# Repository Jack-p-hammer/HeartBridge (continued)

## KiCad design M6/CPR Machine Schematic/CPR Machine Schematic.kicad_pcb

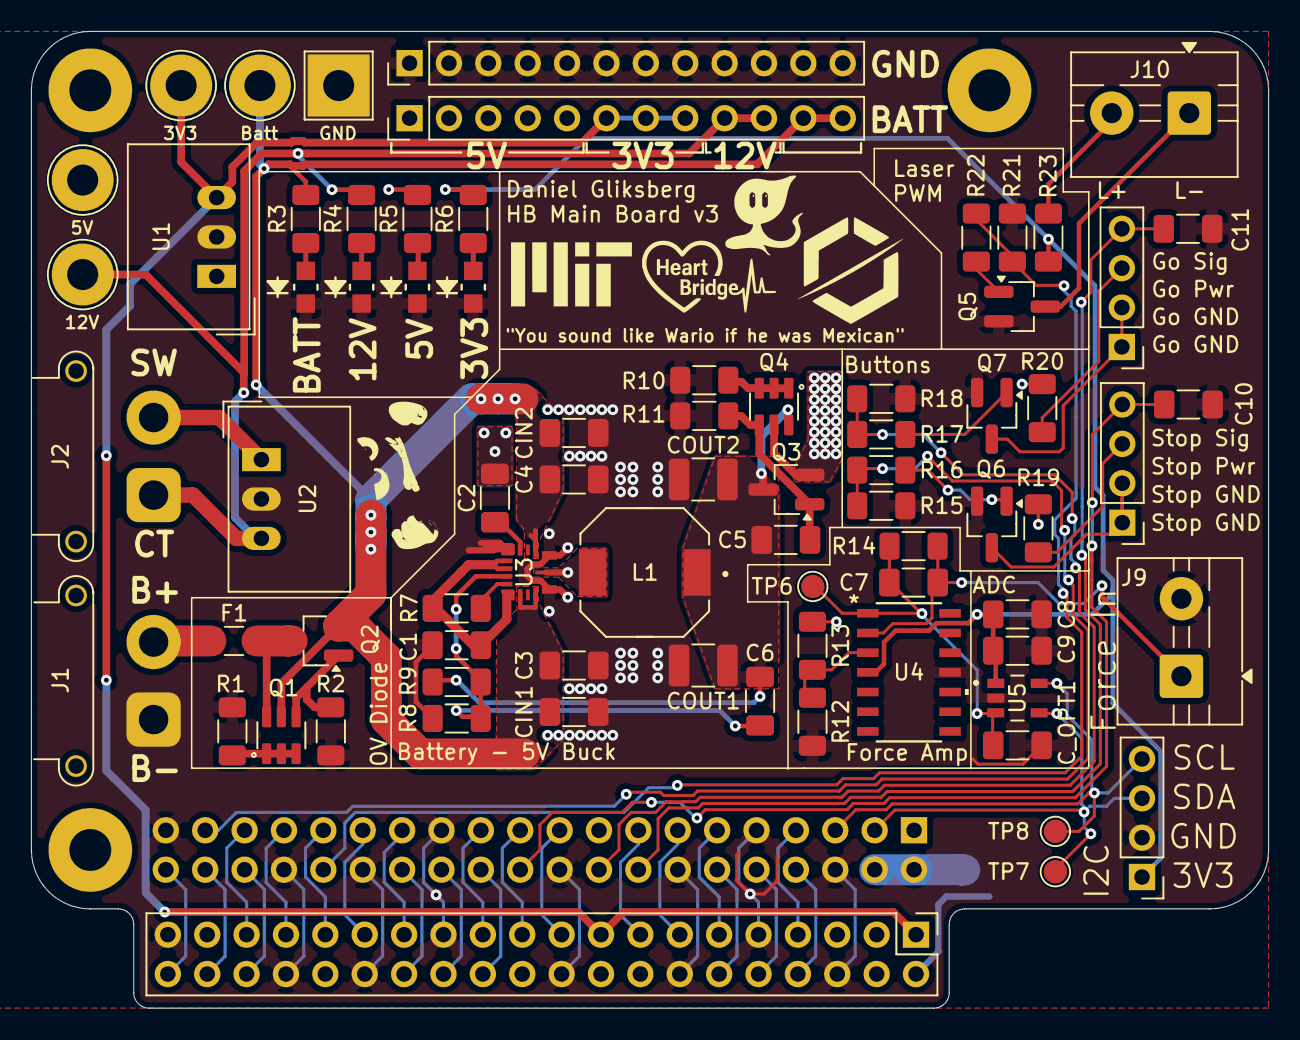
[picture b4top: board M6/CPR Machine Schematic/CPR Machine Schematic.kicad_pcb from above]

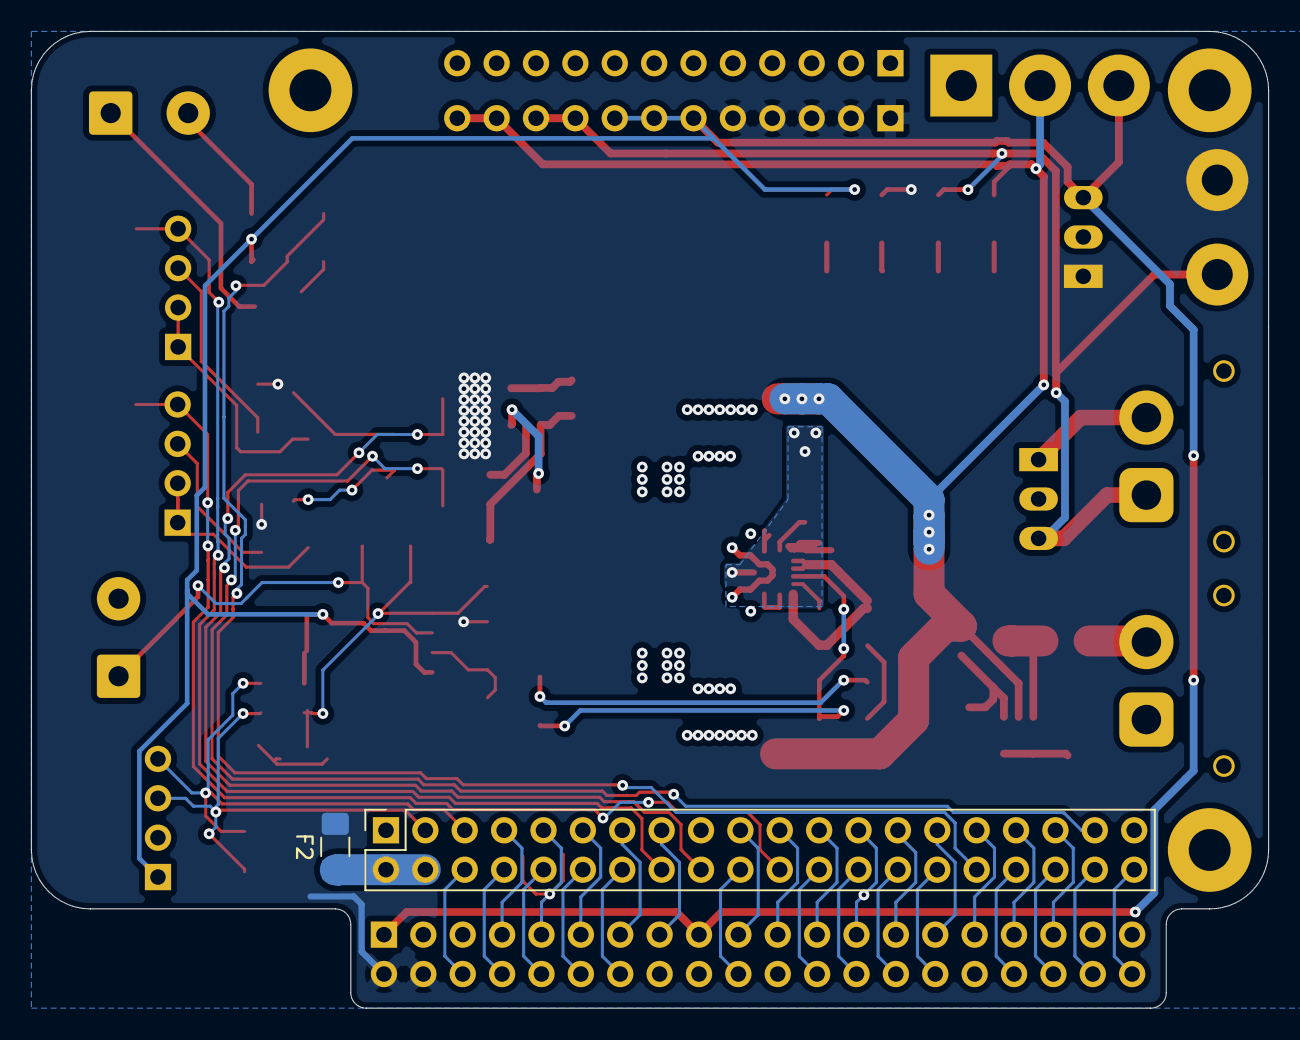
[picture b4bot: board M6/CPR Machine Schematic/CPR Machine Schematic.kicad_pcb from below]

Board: 2 copper layers, 79.8 x 63.0 mm, 80 parts (2 on the bottom side), 63 nets.

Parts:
C1: 2.2 uF; C_1206_3216Metric_Pad1.33x1.80mm_HandSolder
C2, C3, C4, C9: 0.1 uF; C_1206_3216Metric_Pad1.33x1.80mm_HandSolder
C5: 10 nF; C_1206_3216Metric_Pad1.33x1.80mm_HandSolder
C6, C7: 47 pF; C_1206_3216Metric_Pad1.33x1.80mm_HandSolder
C8: 10 uF; C_1206_3216Metric_Pad1.33x1.80mm_HandSolder
C10, C11: 100 nF; C_1206_3216Metric_Pad1.33x1.80mm_HandSolder
CIN1, CIN2: 2.2 uF; C_1206_3216Metric_Pad1.33x1.80mm_HandSolder
COUT1, COUT2: 23.7 uF; C_1210_3225Metric_Pad1.33x2.70mm_HandSolder
C_OPT1: 47 pF; C_1206_3216Metric_Pad1.33x1.80mm_HandSolder
F1: 4A; Fuse_1206_3216Metric_Pad1.42x1.75mm_HandSolder
F2: 3A; Fuse_1206_3216Metric_Pad1.42x1.75mm_HandSolder
H1, H2, H3: MountingHole; MountingHole_2.7mm_M2.5_Pad
J1: Battery 22.2V IN; AMASS_XT30PW-F_1x02_P2.50mm_Horizontal
J2: Power Switch; AMASS_XT30PW-F_1x02_P2.50mm_Horizontal
J3: GND Spare Headers; PinHeader_1x12_P2.54mm_Vertical
J4: +V Spare Headers; PinHeader_1x12_P2.54mm_Vertical
J5: Conn_02x20_Odd_Even; PinHeader_2x20_P2.54mm_Vertical
J6: I2C Port; PinHeader_1x04_P2.54mm_Vertical
J7: Stop Button Port; PinHeader_1x04_P2.54mm_Vertical
J8: Go Button Port; PinHeader_1x04_P2.54mm_Vertical
J9: Force Sensor; TerminalBlock_MaiXu_MX126-5.0-02P_1x02_P5.00mm
J10: Laser Port; TerminalBlock_MaiXu_MX126-5.0-02P_1x02_P5.00mm
J11: Raspberry_Pi_2_3; PinSocket_2x20_P2.54mm_Vertical
L1: 2.2 uH; IND_1217AS-H-2R2N=P3
LED1, LED2, LED3, LED4: Green; LED_LTST-C170GKT_LTO
Q1, Q4: DMMT5401 PNP; SOT95P285X140-6N
Q2: SSM3J332R; SOT-23_Handsoldering
Q3: DMG2305UX-EV; SOT-23_Handsoldering
Q5, Q6, Q7: T2N7002BK,LM; SOT-23_Handsoldering
R1, R10, R12, R15, R18, R21: 10 kOhm; R_1206_3216Metric_Pad1.30x1.75mm_HandSolder
R2, R11: 47 kOhm; R_1206_3216Metric_Pad1.30x1.75mm_HandSolder
R3: 1.5 kOhm; R_1206_3216Metric_Pad1.30x1.75mm_HandSolder
R4: 665 Ohm; R_1206_3216Metric_Pad1.30x1.75mm_HandSolder
R5: 220 Ohm; R_1206_3216Metric_Pad1.30x1.75mm_HandSolder
R6, R16, R17, R22: 100 Ohm; R_1206_3216Metric_Pad1.30x1.75mm_HandSolder
R7: 20 kOhm; R_1206_3216Metric_Pad1.30x1.75mm_HandSolder
R8: 9.5 kOhm; R_1206_3216Metric_Pad1.30x1.75mm_HandSolder
R9: 49.9 kOhm; R_1206_3216Metric_Pad1.30x1.75mm_HandSolder
R13: 90 kOhm; R_1206_3216Metric_Pad1.30x1.75mm_HandSolder
R14: 80.6 kOhm; R_1206_3216Metric_Pad1.30x1.75mm_HandSolder
R19, R20: 49.9 Ohm; R_1206_3216Metric_Pad1.30x1.75mm_HandSolder
R23: 0 Ohm; R_1206_3216Metric_Pad1.30x1.75mm_HandSolder
TP1: 12 V; TestPoint_THTPad_D4.0mm_Drill2.0mm
TP2: 5 V; TestPoint_THTPad_D4.0mm_Drill2.0mm
TP3: 3V3; TestPoint_THTPad_D4.0mm_Drill2.0mm
TP4: Battery; TestPoint_THTPad_D4.0mm_Drill2.0mm
TP5: GND; TestPoint_THTPad_4.0x4.0mm_Drill2.0mm
TP6: Amp Out; TestPoint_Pad_D1.5mm
TP7: SDA; TestPoint_Pad_D1.5mm
TP8: SCL; TestPoint_Pad_D1.5mm
U1: 3.3V Buck; Converter_DCDC_TRACO_TSR-1_THT
U2: 12V Buck; Converter_DCDC_TRACO_TSR-1_THT
U3: MAX42403AFLB+; 21-100701_90-100241_ADI
U4: MCP6004; SOIC14_SL_MCH
U5: MCP3021A5T-E_OT; IC_MCP3021A0T-E_OT

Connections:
+3.3V: C8.2, C9.2, J4.6, J4.7, J4.8, J5.1, J5.17, J6.1, R6.2, R23.1, TP3.1, U1.3 (Vout), U4.4 (V+), U5.1 (VDD)
+5V: F2.1, J4.1, J4.2, J4.3, J4.4, J4.5, J5.2, J5.4, Q3.2, Q4.5, R5.2, R13.1, R19.2, R20.2, TP2.1, U1.1 (Vin)
+12V: J2.1, J4.9, J4.10, R4.2, TP1.1, U2.3 (Vout)
+22.2V: C3.2, C4.2, CIN1.2, CIN2.2, J4.11, J4.12, Q1.5, Q2.2, R3.2, TP4.1, U3.1 (EN), U3.3 (SUP), U3.7 (SUP)
/HMI_Raspi/Go Button: C11.2, J8.4, J11.16 (GPIO23)
/HMI_Raspi/Go Button Ground: J8.1, J8.2, Q7.3 (D)
/HMI_Raspi/Go LED Power: J8.3, R20.1
/HMI_Raspi/Go_Enable: J11.18 (GPIO24), R17.1, R18.1
/HMI_Raspi/Laser_PWM: J11.32 (PWM0/GPIO12), R21.1, R22.1
/HMI_Raspi/Stop Button: C10.2, J7.4, J11.22 (GPIO25)
/HMI_Raspi/Stop Button Ground: J7.1, J7.2, Q6.3 (D)
/HMI_Raspi/Stop LED Power: J7.3, R19.1
/HMI_Raspi/Stop_Enable: J11.37 (GPIO26), R15.1, R16.1
/Power/BST: C2.2, U3.9 (BST)
/Power/Battery +: F1.1, J1.2
/Power/From Switch: J2.2, U2.1 (Vin)
/Power/LX: C2.1, L1.2, U3.5 (LX)
/Power/Reg OUT: C5.2, C6.2, COUT1.1, COUT2.1, L1.1, Q3.3, Q4.6, R9.1
/Raspi/GPIO0: J5.27, J11.27 (ID_SD/GPIO0)
/Raspi/GPIO1: J5.28, J11.28 (ID_SC/GPIO1)
/Raspi/GPIO4: J5.7, J11.7 (GCLK0/GPIO4)
/Raspi/GPIO5: J5.29, J11.29 (GCLK1/GPIO5)
/Raspi/GPIO6: J5.31, J11.31 (GCLK2/GPIO6)
/Raspi/GPIO7: J5.26, J11.26 (~CE1/GPIO7)
/Raspi/GPIO8: J5.24, J11.24 (~CE0/GPIO8)
/Raspi/GPIO9: J5.21, J11.21 (MISO0/GPIO9)
/Raspi/GPIO10: J5.19, J11.19 (MOSI0/GPIO10)
/Raspi/GPIO11: J5.23, J11.23 (SCLK0/GPIO11)
/Raspi/GPIO13: J5.33, J11.33 (PWM1/GPIO13)
/Raspi/GPIO14: J5.8, J11.8 (GPIO14/TXD)
/Raspi/GPIO15: J5.10, J11.10 (GPIO15/RXD)
/Raspi/GPIO16: J5.36, J11.36 (GPIO16)
/Raspi/GPIO17: J5.11, J11.11 (GPIO17)
/Raspi/GPIO18: J5.12, J11.12 (GPIO18/PWM0)
/Raspi/GPIO19: J5.35, J11.35 (GPIO19/MISO1)
/Raspi/GPIO20: J5.38, J11.38 (GPIO20/MOSI1)
/Raspi/GPIO21: J5.40, J11.40 (GPIO21/SCLK1)
/Raspi/GPIO22: J5.15, J11.15 (GPIO22)
/Raspi/GPIO27: J5.13, J11.13 (GPIO27)
/Raspi/I2C_SCL: J6.4, J11.5 (SCL/GPIO3), TP8.1, U5.5 (SCL)
/Raspi/I2C_SDA: J6.3, J11.3 (SDA/GPIO2), TP7.1, U5.4 (SDA)
/Sensing/Vref: R12.1, R13.2, U4.3 (+)
GND: C1.1, C3.1, C4.1, C8.1, C9.1, C10.1, C11.1, CIN1.1, CIN2.1, COUT1.2, COUT2.2, C_OPT1.1, J1.1, J3.1, J3.2, J3.3, J3.4, J3.5, J3.6, J3.7, J3.8, J3.9, J3.10, J3.11, J3.12, J5.6, J5.9, J5.14, J5.20, J5.25, J5.30, J5.34, J5.39, J6.2, J9.2, J11.6 (GND), J11.9 (GND), J11.14 (GND), J11.20 (GND), J11.25 (GND), J11.30 (GND), J11.34 (GND), J11.39 (GND), LED1.1, LED2.1, LED3.1, LED4.1, Q5.2 (S), Q6.2 (S), Q7.2 (S), R1.2, R2.2, R8.2, R10.2, R11.2, R12.2, R15.2, R18.2, R21.2, TP5.1, U1.2 (GND), U2.2 (GND), U3.4 (PGND), U3.6 (PGND), U3.10 (GND), U4.11 (V-), U5.2 (VSS)
unnamed: C5.1, Q3.1, Q4.4, R11.1
unnamed: F1.2, Q1.6, Q2.3
unnamed: F2.2, J11.2 (5V), J11.4 (5V)
unnamed: C7.1, J9.1, R14.2, U4.2 (-)
unnamed: J10.1, Q5.3 (D)
unnamed: J10.2, R23.2
unnamed: LED1.2, R4.1
unnamed: LED2.2, R3.1
unnamed: LED3.2, R5.1
unnamed: LED4.2, R6.1
unnamed: Q1.1, Q1.2, Q1.3, R1.1
unnamed: Q1.4, Q2.1, R2.1
unnamed: Q4.1, Q4.2, Q4.3, R10.1
unnamed: Q5.1 (G), R22.2
unnamed: Q6.1 (G), R16.2
unnamed: Q7.1 (G), R17.2
unnamed: C1.2, R7.2, U3.11 (BIAS), U3.12 (SPS), U3.15 (SYNC)
unnamed: C6.1, R8.1, R9.2, U3.13 (FB)
unnamed: R7.1, U3.14 (PGOOD)
unnamed: C7.2, C_OPT1.2, R14.1, TP6.1, U4.1, U5.3 (AIN)

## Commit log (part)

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2026-03-29 Battery Tracking
2026-03-29 Audio buzzing fixed
2026-04-28 Final PCB
2026-05-07 PCB V1 Final
2026-05-10 Code V3 Start
2026-05-11 Barebones state machine
2026-05-19 test for pulling on pi
2026-05-19 Uploaded images and audio files
2026-05-19 Set up package management
2026-05-19 Package Management part 2
2026-05-19 attempting to sensor
2026-05-19 AV Initialization
2026-05-19 Image Display maybe?
2026-05-19 Some file structure refactoring
2026-06-02 Start of Board V2
2026-06-02 Fixed edge cuts
2026-06-07 Board V2
2026-06-12 Board V2 Final
2026-06-18 Printing Files
2026-06-18 middle printing file
2026-06-22 more printing files
2026-06-26 Final PCB V2
2026-06-28 Python code started
    run:
    pip install -r requirements.txt
    in the project directory on your device to download required packages
2026-06-28 File structure, claude-ed code port
2026-06-28 asset path comment
2026-06-28 Make device log its own directory
2026-06-28 One comment
2026-06-28 Pre-created log file
2026-06-28 Log file directory resolve(), state machine changes
2026-06-28 File path resolve()s, typecasting
2026-06-29 moteus module
2026-06-29 autopep8 formatting
2026-06-29 gitignore, readme, and updated module requirements
2026-06-29 Testing framework
2026-06-29 logs now timestamped
2026-06-29 comments about logging vs printing
2026-06-29 Voltage readout, MUX, Debouncing Caps
2026-06-30 MUX, Debounce Caps, I2C Testpoints
2026-06-30 slight pcb changes
2026-06-30 I2C Scanner script
2026-06-30 Change placeholder pins to real pins
2026-06-30 Added reading functionality for IMU and ToF
